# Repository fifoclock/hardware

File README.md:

# FIFO Hardware
KiCAD Schematics, Footprints, PCB files, and LCSC BOM.

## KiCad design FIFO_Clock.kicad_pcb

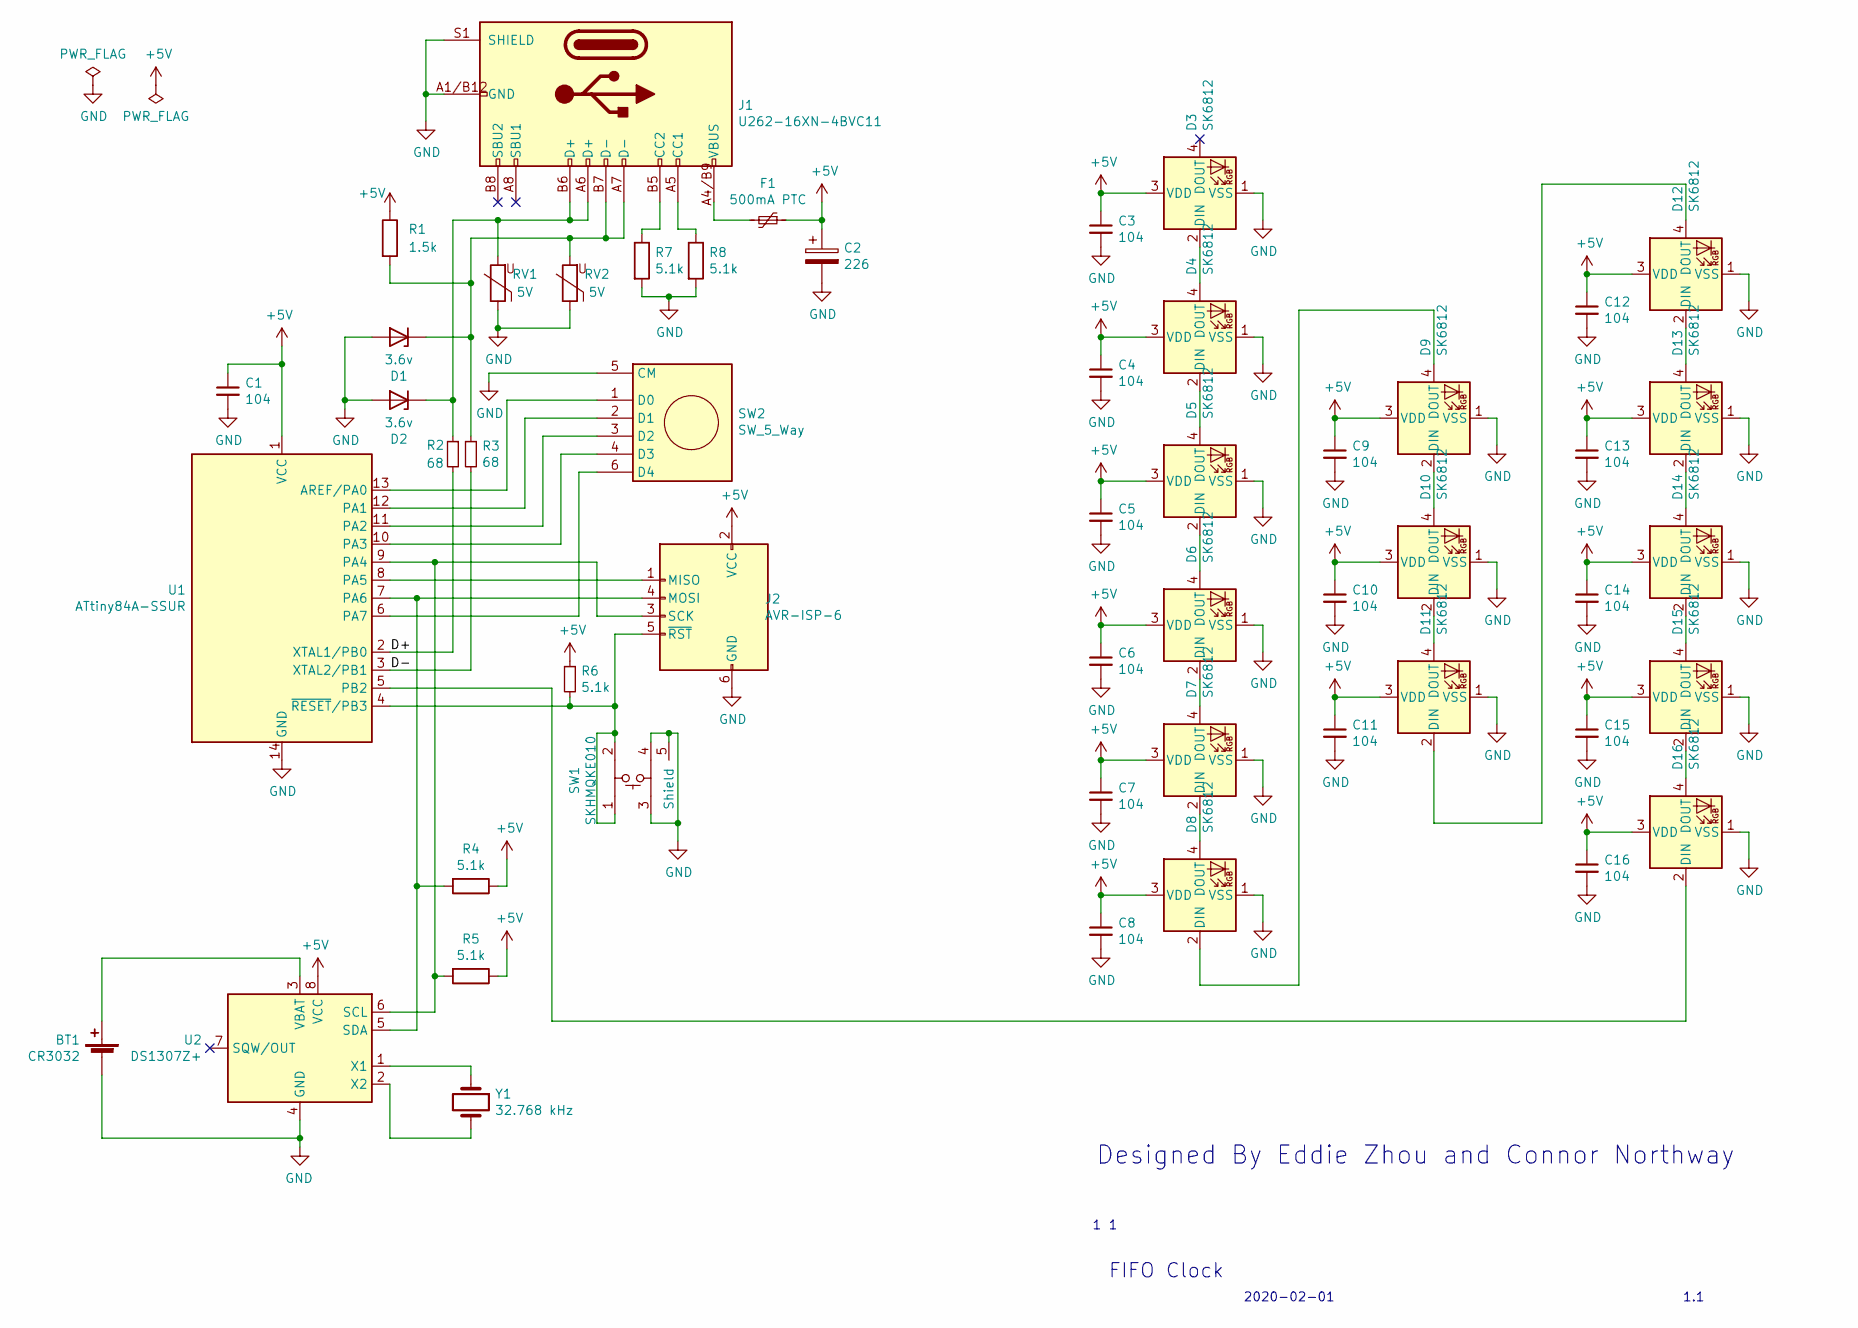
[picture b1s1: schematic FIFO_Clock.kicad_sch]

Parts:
BT1: CR3032; BS-2-1
C1, C3, C4, C5, C6, C7, C8, C9, C10, C11, C12, C13, C14, C15, C16: 104; C_0603_1608Metric_Pad1.05x0.95mm_HandSolder
C2: 226; CP_Elec_6.3x5.8
D1, D2: 3.6v; D_SOD-123
D3, D4, D5, D6, D7, D8, D9, D10, D11, D12, D13, D14, D15, D16: SK6812; LED_SK6812_PLCC4_5.0x5.0mm_P3.2mm_STEALTH
F1: 500mA PTC; Fuse_0805_2012Metric
J1: U262-16XN-4BVC11
J2: AVR-ISP-6; PinHeader_2x03_P2.54mm_Vertical
R1: 1.5k; R_0603_1608Metric_Pad1.05x0.95mm_HandSolder
R2, R3: 68; R_0603_1608Metric_Pad1.05x0.95mm_HandSolder
R4, R5, R6, R7, R8: 5.1k; R_0603_1608Metric_Pad1.05x0.95mm_HandSolder
RV1, RV2: 5V; R_0603_1608Metric_Pad1.05x0.95mm_HandSolder
SW1: SKHMQKE010
SW2: SW_5_Way; K1-5203UA-01
U1: ATtiny84A-SSUR; SOIC-14_3.9x8.7mm_P1.27mm
U2: DS1307Z+; SOIC-8_3.9x4.9mm_P1.27mm
Y1: 32.768 kHz; Crystal_DS26_D2.0mm_L6.0mm_Horizontal

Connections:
+5V: C1.1, C2.1, C3.1, C4.1, C5.1, C6.1, C7.1, C8.1, C9.1, C10.1, C11.1, C12.1, C13.1, C14.1, C15.1, C16.1, D3.3 (VDD), D4.3 (VDD), D5.3 (VDD), D6.3 (VDD), D7.3 (VDD), D8.3 (VDD), D9.3 (VDD), D10.3 (VDD), D11.3 (VDD), D12.3 (VDD), D13.3 (VDD), D14.3 (VDD), D15.3 (VDD), D16.3 (VDD), F1.1, J2.2 (VCC), R1.1, R4.1, R5.1, R6.1, U1.1 (VCC), U2.8 (VCC)
/D+: R2.2, U1.2 (XTAL1/PB0)
/D-: R3.2, U1.3 (XTAL2/PB1)
GND: BT1.2 (-), C1.2, C2.2, C3.2, C4.2, C5.2, C6.2, C7.2, C8.2, C9.2, C10.2, C11.2, C12.2, C13.2, C14.2, C15.2, C16.2, D1.2 (A), D2.2 (A), D3.1 (VSS), D4.1 (VSS), D5.1 (VSS), D6.1 (VSS), D7.1 (VSS), D8.1 (VSS), D9.1 (VSS), D10.1 (VSS), D11.1 (VSS), D12.1 (VSS), D13.1 (VSS), D14.1 (VSS), D15.1 (VSS), D16.1 (VSS), J1.A1/B12 (GND), J1.A12/B1 (GND), J1.S1 (SHIELD), J2.6 (GND), R7.2, R8.2, RV1.1, RV2.1, SW1.3, SW1.4, SW1.5 (Shield), SW2.5 (CM), U1.14 (GND), U2.4 (GND)
unnamed: BT1.1 (+), U2.3 (VBAT)
unnamed: D1.1 (K), J1.A7 (D-), J1.B7 (D-), R1.2, R3.1, RV2.2
unnamed: D2.1 (K), J1.A6 (D+), J1.B6 (D+), R2.1, RV1.2
unnamed: D3.2 (DIN), D4.4 (DOUT)
unnamed: D4.2 (DIN), D5.4 (DOUT)
unnamed: D5.2 (DIN), D6.4 (DOUT)
unnamed: D6.2 (DIN), D7.4 (DOUT)
unnamed: D7.2 (DIN), D8.4 (DOUT)
unnamed: D8.2 (DIN), D9.4 (DOUT)
unnamed: D10.2 (DIN), D11.4 (DOUT)
unnamed: D9.2 (DIN), D10.4 (DOUT)
unnamed: D11.2 (DIN), D12.4 (DOUT)
unnamed: D12.2 (DIN), D13.4 (DOUT)
unnamed: D13.2 (DIN), D14.4 (DOUT)
unnamed: D14.2 (DIN), D15.4 (DOUT)
unnamed: D15.2 (DIN), D16.4 (DOUT)
unnamed: D16.2 (DIN), U1.5 (PB2)
unnamed: F1.2, J1.A4/B9 (VBUS), J1.A9/B4 (VBUS)
unnamed: J1.A5 (CC1), R8.1
unnamed: J1.B5 (CC2), R7.1
unnamed: J2.1 (MISO), U1.8 (PA5)
unnamed: J2.3 (SCK), R5.2, U1.9 (PA4), U2.6 (SCL)
unnamed: J2.4 (MOSI), R4.2, U1.7 (PA6), U2.5 (SDA)
unnamed: J2.5 (~RST), R6.2, SW1.1, SW1.2, U1.4 (~RESET/PB3)
unnamed: SW2.1 (D0), U1.13 (AREF/PA0)
unnamed: SW2.2 (D1), U1.12 (PA1)
unnamed: SW2.3 (D2), U1.11 (PA2)
unnamed: SW2.4 (D3), U1.10 (PA3)
unnamed: SW2.6 (D4), U1.6 (PA7)
unnamed: U2.1 (X1), Y1.1
unnamed: U2.2 (X2), Y1.2

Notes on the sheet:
FIFO Clock
2020-02-01
Designed By Eddie Zhou and Connor Northway
1.1

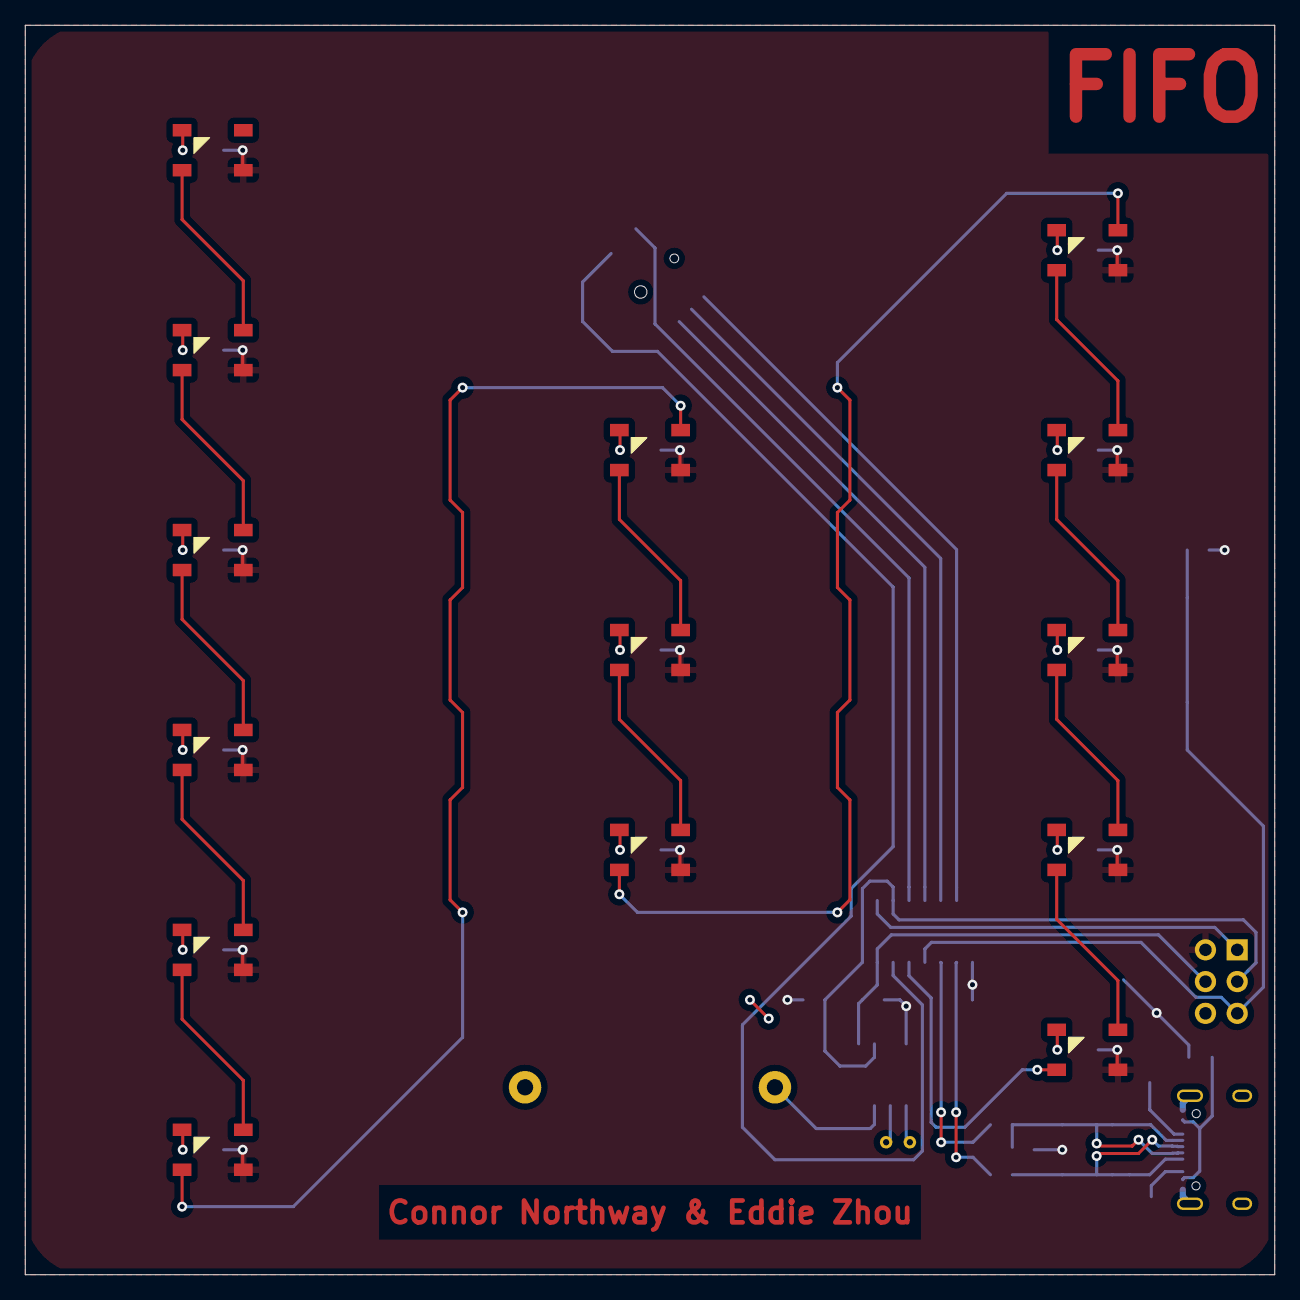
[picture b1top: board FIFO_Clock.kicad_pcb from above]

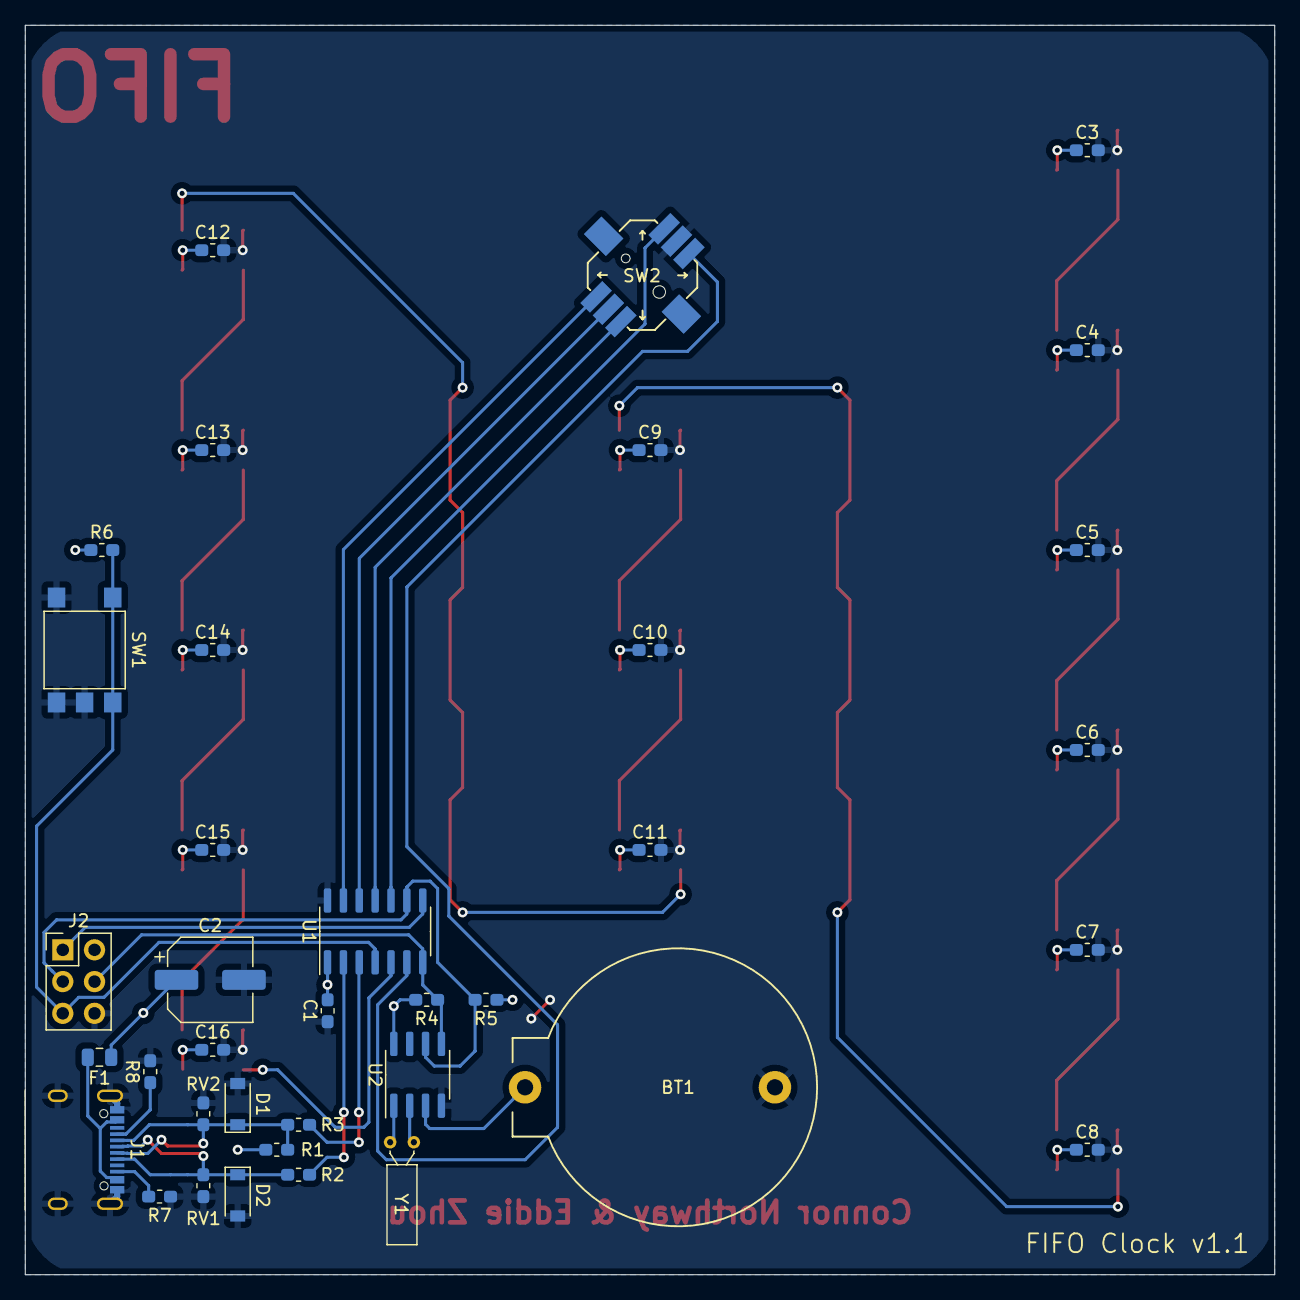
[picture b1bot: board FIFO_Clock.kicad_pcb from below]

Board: 2 copper layers, 100.0 x 100.0 mm, 51 parts (37 on the bottom side), 35 nets.

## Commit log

2019-04-05 modify gitignore to include cache and rescue libs
2019-04-05 initial commit / move to github from google drive
2019-04-13 Finalize USB and Power, and update LED layout
    - add usb circuitry
    - esd protection w/ varistors
    - logic level shifting w/ zener diodes
    - usb protocol pullup/down resistors
    - usb series data resistors
    - update LED layout (now 6-3-5)
2019-04-15 modify resistor values
    changed i2c and reset pullups to 5.1k to match usb cc pulldown.
    allows for easier sourcing of parts
2019-04-15 reverse direction of zener diodes
    v-usb spec has them pointing away from ground:
    http://vusb.wikidot.com/hardware
2019-04-22 Add type-c footprint
    also initialize footprint library for future footprints
2019-04-23 use core libraries for type c connector symbol
    Some files seem to have changed format due to the change between
    5.0.0 and 5.1.0 of KiCad. This is reflected in this commit
2019-04-23 remove fp-info-cache, add to .gitignore
2019-04-23 add annotations and power flags
2019-04-23 update type c receptacle footprint
    add silkscreen line for front of connector
    move silkscreen reference and fab reference
2019-04-23 initial commit of alps switch footprint
2019-04-25 fix pin numbering of SKHMQKE010
2019-04-25 add SKHMQKE010 symbol
2019-04-26 add BS-2-1 battery holder
    - estimation of silkscreen because datasheet is badly dimensioned
    (trig and rounding was involved)
    - courtyard for added safety in case it's a few parts of a mm off
    - unknown if pins are correctly numbered yet
2019-04-26 fix overlapping silkscreen w/ copper in BS-2-1 footprint
2019-04-28 Add 5-way switch footprint
    pin 5 is ground
2019-04-29 change reset switch in schematic
2019-04-29 Fix 5 way switch symbol pin labels
2019-04-29 Delete extra i2c junction
    Hopefully I didn't break anything with the project component library
2019-04-29 Change duplicate pin 5 to pin 6 on 5-way switch
2019-04-29 assign footprints and create netlist
    also remove netlist from .gitignore
2019-04-30 fix usb c connector by stacking redundant pads
    also update netlist
2019-04-30 Create custom symbol for usb receptacle
2019-04-30 annotate usb receptacle and regen netlist
2019-04-30 move origin of usb-c receptacle to edge
    for easier placement later
2019-04-30 fix 5-way switch pads
    the pads did not have their origin at the center which makes
    connecting traces extremely difficult. moved the origin of each
    pad to the center of the pad
2019-04-30 begin pcb layout
    - basic layout of LEDs, usb conn, battery, etc
    - battery may interfere with future mounting hole
    - traces between LEDs and between LEDs and caps
    - general idea of where to place passives around usb conn.
    - began routing between attiny, switch, battery and rtc
    - likely too eager, feel free to rip up. Will likely need to
2019-04-30 fix smd pads in type c receptacle footprint
2019-04-30 Create 2 sided SMD design (only LEDs on front)
2019-04-30 Add LCSC BOM
2019-04-30 Add B side usb data lines
2019-04-30 Flip crystal footprint
2019-05-01 an attempt at better placement for right edge
    (icsp header, switches, power circuitry)
2019-05-02 Finish pcb routing
2019-05-02 Fix led and trace alignment
2019-05-02 Center 5 way switch
2019-05-02 Refresh fills
2019-05-02 fix annotations and silkscreen locations
2019-05-02 fix copper pour
2019-05-03 silkscreen and stealth labels
    add a stealth footprint for the leds because we dont need silkscreen
    on the front
    official name is FILO Clock
    first illuminated last out
    .. or ..
    first ignited last out
2019-05-03 create gerber files for manufacturing
2019-05-06 Remove unused kicad pcb layout
2019-05-06 Rename pcb layout to match project
2019-05-06 Remove unused KiCAD project file
2019-06-03 Update BOM to match final order
2019-06-03 Rename KiCAD project to FILO_Clock
2020-01-13 v1.1 changes transferred, FILO->FIFO change
2020-02-01 change schematic to US letter, add image to README
2020-02-01 update readme wording
2020-02-01 Create LICENSE
2023-02-17 Fix usb CC pulldown circuit
    make sure to use two pulldown resistors instead of shorting CC lines
    found this while trying to repurpose one of the old pcbs for something else
    <x> years later I have a slightly better understanding of the USB spec..
2023-02-17 remove gerbers
    out of date, and it's better to not have generated outputs in the repo anyway
